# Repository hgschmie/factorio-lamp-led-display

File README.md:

# Factorio Lamp LED Display

Adds a mod to the Factorio game (2.1 version needed) that sends out UDP packets to a local receiver daemon. The daemon creates MQTT messages that can be picked up by embedded microcontrollers that in turn drive Neopixel LEDs which reflect the color and status of in-game Lamps.

Factorio -> UDP to local receiver -> daemon (golang code) -> MQTT (mosquitto broker) -> ESP32-C3 receiver -> Neopixel LEDs

This repository contains most of the pieces required to build this. You need to bring some skills/tools though:

- at least breadboarding, better soldering for the hardware
- a 3D printer to make the Lamp cases
- a local docker installation on the machine where you run Factorio (or you need to run the daemon manually, it is a single binary)

What you find:

- `daemon` contains the golang code for the local receiver daemon
- `factorio-mod` contains the code for the [Lamp LED Display](https://mods.factorio.com/mod/lamp_led_display) mod. Or get it from the mod portal
- `firmware` contains the software for the ESP32-C3 supermini board
- `pcb` contains the KiCAD files for a controller board. Or you can breadboard this together, either works fine.
- `3dprint` contains the 3MF files for the Lamp.

## How to get it to work

(All of this is intended to be run in a local network that is firewalled/secured against the internet. There is little security besides bare-bones passwords that are written in cleartext in config files locally. If you care deeply about security, there is room for improvement)

### Local setup

This sets up runtime config, broker credentials and starts the daemon.

```sh
cp config.example.yaml config.yaml
./scripts/create-credentials.sh
docker compose up -d --build
```

The `config.yaml` file is read by the daemon on startup. The secrets created by the script are stored in the `secrets` directory.

If everything goes well, this is what docker ps should show:

```text
❯ docker ps
CONTAINER ID   IMAGE                      COMMAND                  CREATED       STATUS       PORTS                                         NAMES
208767bb72bf   display-daemon             "/factorio-display"      6 hours ago   Up 6 hours   127.0.0.1:34198->34198/udp                    display-daemon-1
9c2e8b83e011   eclipse-mosquitto:2.0.22   "/docker-entrypoint.…"   6 hours ago   Up 6 hours   0.0.0.0:1883->1883/tcp, [::]:1883->1883/tcp   display-mosquitto-1
```

### Factorio Setup

- add the mod from the mod portal (or copy the `factorio-mod/lamp_led_display` folder into your mod folder). Add `--enable-lua-udp 34199` to the Factorio start command. If you run Factorio from Steam, you can add this to the "Launch Options" directly in Steam.

- Start Factorio and load a game that has the mod activated. Then run `docker logs -f display-daemon-1` from a command line window. You should see something like this:

```text
daemon-1     | {"time":"2026-08-27T01:00:59.183286626Z","level":"INFO","msg":"factorio packet accepted","save_id":"1f0288b3-4937613a","sequence":1,"type":"snapshot","channels":0}
```

If you see this, congrats, Factorio is talking to the locally running daemon and writes MQTT messages.

### Get some LEDs

Make sure to get an ESP32-C3 supermini board (most other ESP32-C3 boards should work, too).

- Install the PlatformIO framework. On a mac, do `brew install platformio`. Otherwise, go to [PlatformIO Core installation](https://platformio.org/install/cli) and follow the instructions

- connect your board to the computer with an USB cable

- run

```sh
cd firmware
pio run -e esp32-c3-supermini -t upload
pio device monitor
```

If all goes well, you should see a `Factorio-Display-xxxxxx` WiFi network appear. Connect to it (e.g. with a smartphone), it should pop open a capturing portal to enter WiFi credentials, MQTT broker information. Leave the pixel count as "8" and the "channel offset" as 0. Save, reboot and now the device should show (in the shell that does the `pio device monitor`) something like this:

```text
Connected!
*wm:AutoConnect: SUCCESS
*wm:STA IP Address: 172.16.10.102
Configuration page: http://172.16.10.102/ or http://factorio-display-shop-floor-a.local/
```

running `docker logs display-mosquitto-1` should show something like this:

```text
1787807093: New client connected from 192.168.65.1:46373 as factorio-display-shop-floor-a (p2, c1, k30, u'device').
```

### Assign a lamp

If you have any Neopixels connected to the ESP32-C3 chip, you are now ready to assign a lamp to them. If you are not running the game right now, after a few seconds, all LEDs should start to slowly pulse cyan to show that "no Factorio game is sending any information". This also happens when you pause the game.

Put a Lamp down, give it some color, make sure that "always on" is checked.

Press ALT/Option + Shift + D. The cursor should now show a lamp.

Click on the Lamp you just placed. In the dialog, set the Channel Number to "1". PRESS ENTER!

The first LED on your ESP32-C3 should now have the same color as the lamp in the game.

Press Control + Shift + D to open the Channel list where you can control other aspects or delete a channel.

----

## Project background

This project owes its existence to the lucky confluence of a few things.

- I found a Factorio Lamp on Makerworld that is designed for RGB (Neopixel) LEDs.
- I really wanted to play around with ESP32-C3 Supermini boards and I had a few lying around.
- Adafruit sells nice 5mm discrete multi-color LEDs that are Neopixel compatible.

And while all of this is great, some obstacles were in the way:

- The Factorio Lamp was single-color white and not gray/translucent. So some remixing was required.
- Besides 3D printing, this project requires some hardware and quite a bit of software.
- Firmware for the ESP32-C3
- Some daemon that takes UDP from Factorio and sends it to the board
- An actual Factorio mod that sends out UDP data messages.

That project was shelved for a year or so. Not much happened.

__If you are concerned about AI and can no longer sit back and allow AI infiltration, AI indoctrination, AI subversion and the international AI conspiracy to sap and impurify all of your precious bodily fluids, then this is the moment where you need to stop reading.__

----

I read [Matthew Brunelle's Blog](https://blog.matthewbrunelle.com/its-ok-to-use-coding-assistance-tools-to-revive-the-projects-you-never-were-going-to-finish/) and a new AI model arrived (GPT-5.6-sol if you are interested) and anyway, I wanted to find out how good AI really is.

I resurrected that project with a single prompt (typos and all):

```text
"here is what I want to do: I play the game factorio and I want to bring some of the aspects of the game to the real world. For that, I want to connect a few multi-color LEDs to a microcontroller, which can connect to WiFi. The factorio game should send some events out through its UDP interface to a local daemon (same host where the game runs) which in turn can turn these LEDs on and off.

I have a bunch of ESP-C3 microcontrollers, NeoPixel LEDs and passive components that would be needed to breadboard that together. I want to use the PlatformIO for the framework. The code on the ESP-C3 should allow me to configure WiFi when it boots up, then connect to a daemon running on my host using MQTT. In the long run, it should be possible to have multiple microcontrollers. The code on the microcontroller can be written in C or Rust, the daemon should be written in golang. If you have any questions, ask me, then create a plan on what we want to do."
```

~ 15 clarification questions and 20 Minutes later, I had about ~75% of this git repo. It went through a few iterations (some protocol additions, simplification of configuration, adding configuration pages to the microcontroller) afterwards.

And it worked on the first try.

It put together some documentation (the contents of the [docs folder](https://github.com/hgschmie/factorio-lamp-led-display/tree/main/docs) and the [README-codex](https://github.com/hgschmie/factorio-lamp-led-display/blob/main/README-codex.md)). None of those are 100% correct but pretty close.

What this project contains is not just AI generated code. I rewrote the factorio mod from scratch (the AI generated one was functional but ugly and iterating a few times made the code very convoluted) and while I got ChatGPT to put together ~50% of the PCB (KiCAD MCP is difficult to get to work but once it does, codex gets a lot done with it), I ultimately re-layouted it and routed it manually.

AI put together all of the tests (and updated them once I rewrote the factorio mod), the docker setup, all scripts and the docs. It verified the things I did and pointed out errors that I did not notice.

But I never touched (nor read) the ESP32-C3 firmware and the UDP daemon code. And the firmware has way more feature that I would have built myself (configuration pages! mDNS!). I assume the code is ugly for a human but so is the compiler output from a high level language compiler.

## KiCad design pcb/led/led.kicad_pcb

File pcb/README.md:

# PCB

This directory contains the KiCad project for the eight-channel LED interface board and the LED adapter

## Interface Board (pcb folder)

### Project files

- `pcb.kicad_pro`, `pcb.kicad_sch`, and `pcb.kicad_pcb` are the KiCad project, schematic, and board layout.
- `display_parts.kicad_sym`, `display_parts.pretty/`, `sym-lib-table`, and `fp-lib-table` are the project-local symbol and footprint libraries.
- `fabrication-toolkit-options.json` contains settings for the optional Fabrication Toolkit plugin.
- `production/` is generated output and is not an editable source of the design.

Open `pcb.kicad_pro` in KiCad. Use the Schematic Editor to change the circuit, then run **Inspect → Electrical Rules Checker**. Transfer changes with **Tools → Update PCB from Schematic**, finish placement and routing in the PCB Editor, refill copper zones, and run **Inspect → Design Rules Checker**. Resolve all DRC errors before ordering.

### Creating fabrication files

Save the project before exporting. In the PCB Editor, use **File → Fabrication Outputs** to create:

- Gerbers for `F.Cu`, `B.Cu`, `F.Mask`, `B.Mask`, `F.Silkscreen`, `B.Silkscreen`, and `Edge.Cuts`;
- separate plated and non-plated Excellon drill files;
- paste layers only when ordering a solder stencil;
- a BOM and component-position file only when ordering assembly.

Alternatively, if the Fabrication Toolkit plugin is installed, run it from **Tools → External Plugins** and export into `production/`. Zip the Gerber and drill files together and upload that archive to the PCB manufacturer. Check the manufacturer's Gerber preview, board dimensions, layer count, thickness, and drill holes before placing the order.

KiCad lock files, `pcb-backups/`, `*.kicad_prl`, exported netlists, and files under `production/` are generated or machine-local and do not need to be committed.

## LED Board (led folder)

Soldering the LEDs to wires became cumbersome so I designed another, small board. I ordered 50 of those from both JLCPCB and PCBWAY (and I paid more for shipping than the actual boards).

I used LEDs from adafruit (https://www.adafruit.com/product/1938) but they are expensive and often out of stock. Those can be used with the board but DIn and DOut are swapped compared to the board print. Also, make sure that the ground pin (inner short pin) really is in the right place on the board. These LEDs use RGB order, so the controller must be set accordingly.

I used *WAY MORE* shockingly cheap (~$.24 compared to roughly $1 from adafruit) LEDs from Amazon (https://www.amazon.com/dp/B0H87Y196Q). While it looked a bit shady, they came straight from China (8 business days) and work fine. Two caveats, however: a) They have a different color order (GRB). This can be configured on the controller but it means you can not mix with adafruit LEDs. And b) more importantly, those LEDs are really sensitive to be wired up wrong. Almost any LED I ever used can survive a brief wiring error but not those. One mistake and the LED is toast. Double check your connections and order more than the few you need (I mean, they come in 100 packs) because you will fry a few (I fried about a dozen).

The boards show a wire connector but in reality there is not enough space below the 3d printed LED case for that. Solder the wires directly to the board.

Speaking of wires:

Unless you really like crimping dupont connectors (I don't), making the connectors for the LEDs is pretty annoying. I ended up buying breadboard jumper cables (https://www.amazon.com/dp/B0FJXZZM83) and cut off the connectors on one side and soldered them directly onto the LED boards. That leaves you with the problem of four separate, small pins one the other end which are annoying to plug onto the controller board (especially through the opening in the top of the box or the underside of a base plate. Enter https://makerworld.com/en/models/2594713-dupont-connector-bridge which is fantastic for turning four pins into a single connector (with a pin 1 marker! That is really important, see above). Except that it is a tiny bit too tall to fit eight in a row onto the board (if I had discovered those before I ordered the boards, I would have left more space but I did not). So I asked claude to make a slimmer version, which is in the `3dprint/connector` folder.

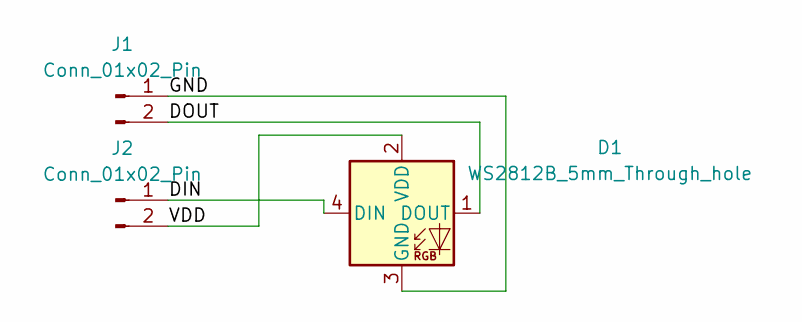
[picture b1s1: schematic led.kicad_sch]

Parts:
D1: WS2812B_5mm_Through_hole; LED_D5.0mm-4_RGB
J1, J2: Conn_01x02_Pin; PinHeader_1x02_P2.54mm_Horizontal

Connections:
/DIN: D1.4 (DIN), J2.1
/DOUT: D1.1 (DOUT), J1.2
/GND: D1.3 (GND), J1.1
/VDD: D1.2 (VDD), J2.2

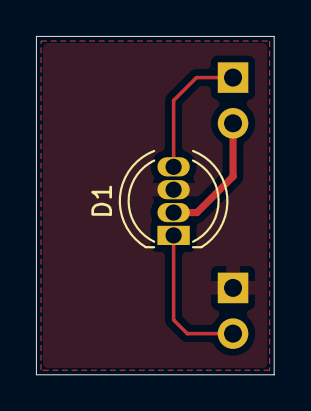
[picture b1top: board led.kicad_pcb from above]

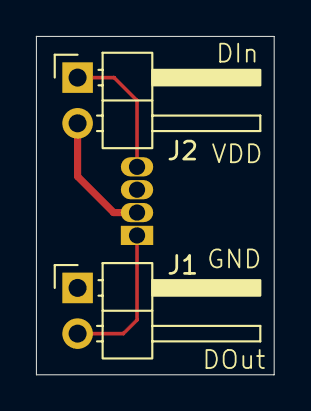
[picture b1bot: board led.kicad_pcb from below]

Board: 2 copper layers, 13.2 x 18.8 mm, 3 parts (2 on the bottom side), 4 nets.

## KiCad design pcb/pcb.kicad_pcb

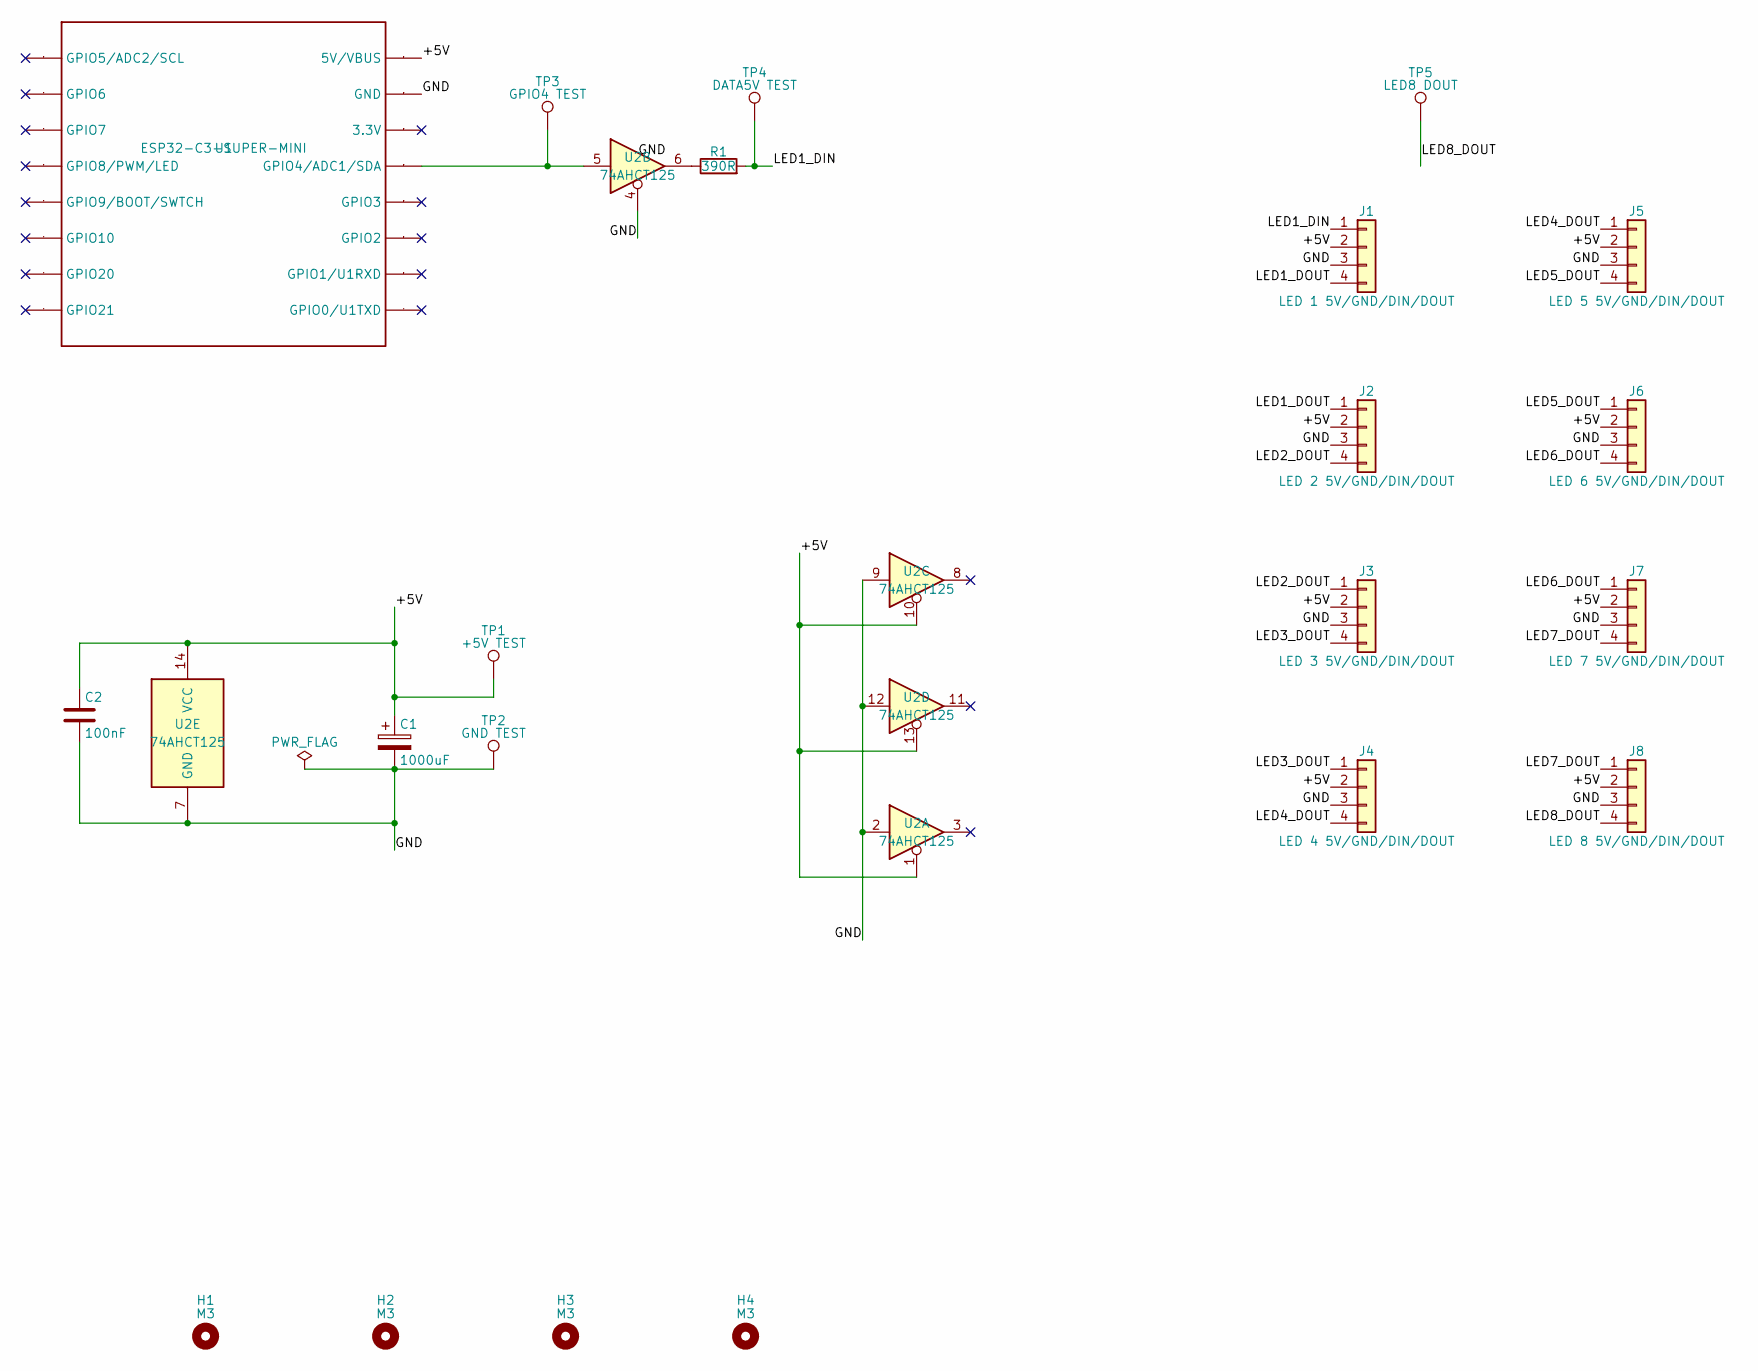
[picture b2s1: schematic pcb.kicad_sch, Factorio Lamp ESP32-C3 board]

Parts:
C1: 1000uF; CP_Radial_D10.0mm_P5.00mm
C2: 100nF; C_Disc_D5.0mm_W2.5mm_P5.00mm
H1, H2, H3, H4: M3; MountingHole_3.2mm_M3
J1: LED 1 5V/GND/DIN/DOUT; PinHeader_1x04_P2.54mm_Vertical
J2: LED 2 5V/GND/DIN/DOUT; PinHeader_1x04_P2.54mm_Vertical
J3: LED 3 5V/GND/DIN/DOUT; PinHeader_1x04_P2.54mm_Vertical
J4: LED 4 5V/GND/DIN/DOUT; PinHeader_1x04_P2.54mm_Vertical
J5: LED 5 5V/GND/DIN/DOUT; PinHeader_1x04_P2.54mm_Vertical
J6: LED 6 5V/GND/DIN/DOUT; PinHeader_1x04_P2.54mm_Vertical
J7: LED 7 5V/GND/DIN/DOUT; PinHeader_1x04_P2.54mm_Vertical
J8: LED 8 5V/GND/DIN/DOUT; PinHeader_1x04_P2.54mm_Vertical
R1: 390R; R_Axial_DIN0207_L6.3mm_D2.5mm_P10.16mm_Horizontal
TP1: +5V TEST; TestPoint_Plated_Hole_D2.0mm
TP2: GND TEST; TestPoint_Plated_Hole_D2.0mm
TP3: GPIO4 TEST; TestPoint_Plated_Hole_D2.0mm
TP4: DATA5V TEST; TestPoint_Plated_Hole_D2.0mm
TP5: LED8 DOUT; TestPoint_Plated_Hole_D2.0mm
U1: ESP32-C3-SUPER-MINI; ESP32-C3-SUPER-MINI-SOCKET
U2: 74AHCT125; DIP-14_W7.62mm_Socket

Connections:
/+5V: C1.1, C2.1, J1.2, J2.2, J3.2, J4.2, J5.2, J6.2, J7.2, J8.2, TP1.1 (1_1), U1.16 (5V/VBUS), U2.1, U2.10, U2.13, U2.14 (VCC)
/GND: C1.2, C2.2, J1.3, J2.3, J3.3, J4.3, J5.3, J6.3, J7.3, J8.3, TP2.1 (1_1), U1.15 (GND), U2.2, U2.4, U2.7 (GND), U2.9, U2.12
/LED1_DIN: J1.1, R1.2, TP4.1 (1_1)
/LED1_DOUT: J1.4, J2.1
/LED2_DOUT: J2.4, J3.1
/LED3_DOUT: J3.4, J4.1
/LED4_DOUT: J4.4, J5.1
/LED5_DOUT: J5.4, J6.1
/LED6_DOUT: J6.4, J7.1
/LED7_DOUT: J7.4, J8.1
/LED8_DOUT: J8.4, TP5.1 (1_1)
unnamed: R1.1, U2.6
unnamed: TP3.1 (1_1), U1.13 (GPIO4/ADC1/SDA), U2.5

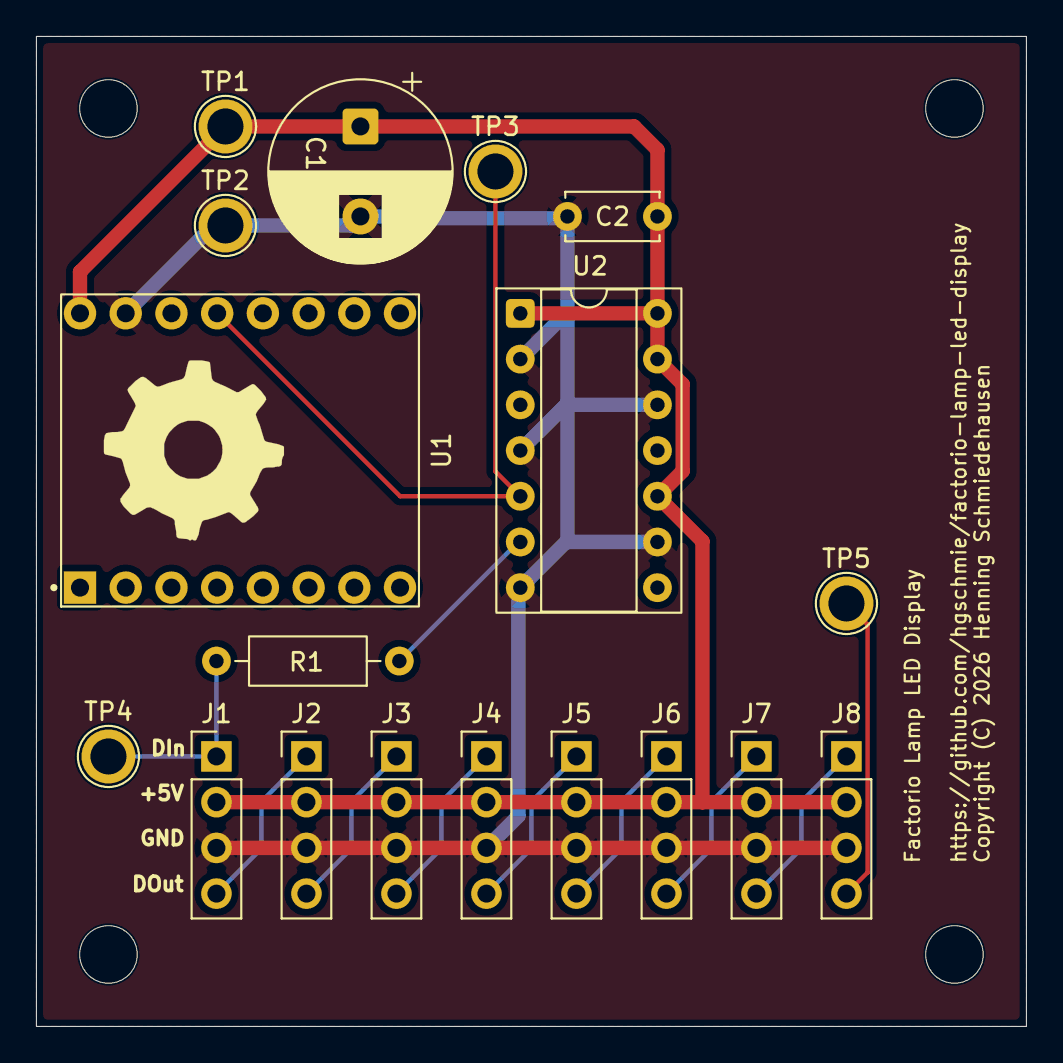
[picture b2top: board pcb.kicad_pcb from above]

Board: 2 copper layers, 55.0 x 55.0 mm, 22 parts (0 on the bottom side), 13 nets.

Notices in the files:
pcb/pcb.kicad_pcb:
Copyright (C) 2026 Henning Schmiedehausen
